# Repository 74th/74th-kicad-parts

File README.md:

# 74th の使う KiCad Parts

- symbols: KiCad のシンボル
- footprints: KiCad のフットプリント
- 3d-models: ダウンロードした 3D モデルを置くディレクトリ
- pcb-default: 基板の設定の標準データ。最初にインポートして使う

## 他によく使う KiCad Parts

- Espressif KiCad Library https://github.com/espressif/kicad-libraries

## あるもの（一例）

### シンボル

- 74th_ApplicationIC
  - CH224K: USB PD Sink Controller
  - CH334R: USB2.0 Hub Controller
  - CH340C, CH340G, CH340X: USB UART
  - CH9329: USB to USBHID Keyboard/Mouse
  - W25Q32JVSS, W25Q32JVUU: Flash
- 74th_Board
  - M5Stack Core2 M-BUS
- 74th_Display
  - OSL01561-LW: 7seg LED
  - I2C OLED Module
- 74th_Interface
  - AudioJack_4_TRRS
  - ESP-Prog_ProgramCOM_Recv
  - Grove Device-Side/Host-Side
  - I2C Breakout
  - I2C Grove Device-Side/Host-Side
  - JoyStick b10k
  - Jumper 2/3
  - Pin 1~20
  - Pin 4 PokaYoke
  - Pin 2 GND
  - ProMicro Left/Right/Left-NoGND
  - Qwiic DeviceSide/HostSide
  - RaspberryPiPico PinOut
  - SWD 3Pin
  - SWD 10Pin Debuger-Side/MCU-Side
  - SWD WCH 1Wire/With VCC/With TXD-VCC
  - SWD LinkE header
  - SW Push
  - SW Push Pin-4
  - SW Slide
  - UART Grove Device-Side/Host-Side
  - UART TX
  - USB TypeA 2.0 Plug
  - USB TypeA 2.0 Receptacle
  - USB TypeC 2.0 Plug
  - USB TypeC 2.0 Receptacle
  - USB TypeC 2.0 Receptacle Simple
  - USB TypeC 3.0 Plug
  - USB TypeC 3.0 Plug 24Pin
- 74th_MCU
  - CH32V002F4P6/F4U6/J4M6
  - CH32V003F4P6/F4U6/J4M6
  - CH32V006K8U6
  - CH32V203CxT6/F6T6
  - CH32V305FBP6
  - CH32X035G8U6
  - RP2040
  - RP2350A
  - RP2350B
  - STM32F103C8T6
  - STM32G030F6P6
- 74th_Passive
  - AMS117-3.3: Regulator
  - AP7333-LDO: Regulator
  - CH213K: USB電源保護IC
  - CH217K: USB電源保護IC
  - IRLM6402: Pch MOSFET
  - MT2492: DCDC Converter
  - SK6812MINI-E : RGB LED
  - MT2492: DCDC COnverter
- 74th_PassiceCommon
  - Crystal_GND24
  - L Directed
  - MOSFET Dural Pch

### footprint

- BatteryHolder CR2034
- Basic
  - Capacitor 0402in_1005M/0603in_1608M/0805in_2012M/1206_3216M
  - Capacitor 0603in_1608M/0805in_2012M WithSizeText
  - Register 0402in_1005M/0603in_1608M/0805in_2012M/1206_3216M
  - Register 0603in_1608M/0805in_2012M WithSizeText
  - Inductor 4.1x4.5mm
  - Inductor 0806in 2016M
- Connector
  - BoxPinHeader 2x03 P1.27 (ESP-Prog)
  - BoxPinHeader 2x05 P1.27 (SWD)
  - Grove or Qwiic Socket
  - HY-2.0 SMD 4Pin/TH-Surface 4Pin/TH Versical 4Pin
  - HalfPinHeader SWD
  - MJ-4PP-9 (TRRSジャック)
  - PH-2.0
  - SH-1.0 SMD 2Pin/4Pin(Qwiic)
  - USB-A Plug TH
  - USB-A Receptacle SMT 4-Pin
  - USB-C Plug 2.0 for 24 Pin
  - USB-C Plug 2.0 24Pin
  - USB-C Receptacle SMT 12-PIn Midmount
  - USB-C Receptacle SMT 12-PIn Midmount Simple
  - USB-C Receptacle SMT 12-PIn Simple
  - USB-Micro Plug SMD
  - USB3-A-Receptacle SMT 9-Pin
- Crystal
  - SMD 2012 2-Pin 2.0x1.2mm HandSoldering
  - SMD 2012 2-Pin 3.2x1.5mm
  - SMD 2012 4-Pin 3.2x1.5mm HandSoldering
- Display
  - OSL10561-LW
- Hole
  - M1.6
  - M2
  - M5Dial/M5Dial Stopper
  - M5StackCore2
  - OLED 0.96inch
- LED
  - 0805in_2016M
  - Reverse Mount 0805in_2016M
  - SK6812MINI-E back side light
  - SK6812MINI-E silk side light
- Mousebite
- Package
  - Fuse 1812in 4532m
  - LQFP-48 7x7mm P0.5 EP1.7x1.7mm
  - QFN-20-1EP 3x3mm P0.5 EP2.6x2.6mm Handsolder
  - QFN-24-1EP 4x4mm P0.4 EP2.8x2.8mm Handsolder
  - QFN-28-1EP 4x4mm P0.4 EP2.7x2.7mm
  - QFN-32-1EP 4x4mm P0.4 EP2.7x2.7mm
  - QFN-32-1EP 4x4mm P0.4 EP2.7x2.7mm Handsolder
  - QFN-54-1EP 7x7mm P0.4 EP3.1x3.1mm Handsolder
  - QFN-60-1EP 7x7mm P0.4 EP3.4x3.4mm Handsolder
  - QFN-80-1EP 10x10mm P0.4 EP3.4x3.4mm Handsolder
  - SOD23 Diode
  - SOD23 Diode No-Reference
  - SOD123W
  - SOIC-8 3.9x4.9mm P1.27mm
  - SOIC-8 3.25x5.23mm P1.27mm
  - SOIC-16 3.8x8.8mm P1.27mm
  - SOT-23
  - SOT-23-5
  - SOT-23-6
  - SOT-89-3
  - SOT233-3
  - TSSOP-20 4.4x6.5mm P0.65mm
  - USON-8 3.4mm P0.8mm
- Pad 1/4
- PinOut
  - Pin 1~20
  - PokeYoke
  - Raspberry Pi Pico
  - ProMicro LIKE LEFT/RIGHT
- SolderJumper-2/3
- Switch
  - MXChocSwap 1Side 1.0u
  - MXChoc 1.0u
  - MXSwapChoc 1.0u
  - MXSwap 1.0u
  - MXSwap 1.25u
  - SKRPABE010
  - SK-12D02-G020
  - TactileSwitch4Foot 6x6

## LICENSE

明記のないものは CC0 (Creative Commons Public License) とします。

いくつかのパーツは KiCad ライブラリーからコピーして使っています。それぞれのディレクトリの README を参照してください。

## Links

- 74thのOpen Source Hardwareのプロジェクト https://github.com/74th/74th-open-source-hardware-projects

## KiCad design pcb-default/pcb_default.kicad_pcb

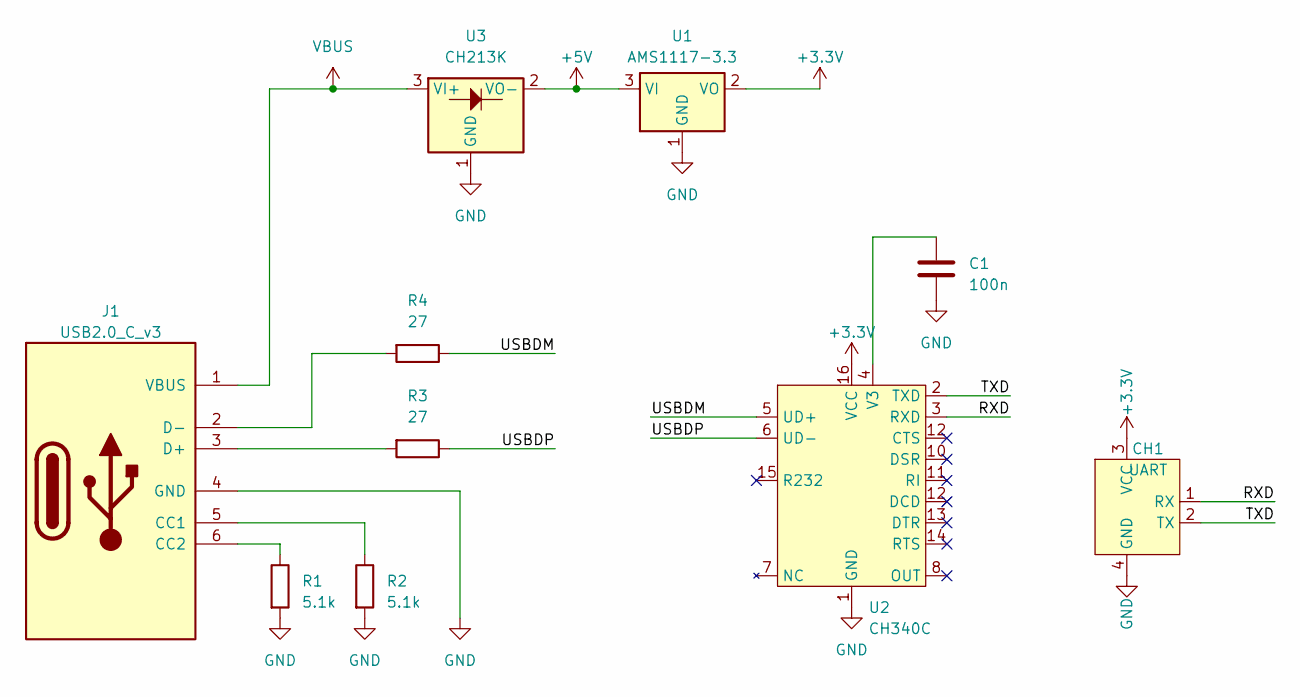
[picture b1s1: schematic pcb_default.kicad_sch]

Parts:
C1: 100n; Capacitor_0805_2012
CH1: UART; Connector_HY-2.0_SMD_4Pin
J1: USB2.0_C_v3; Connector_USB-C-Receptacle_SMT_12-Pin_Simple
R1, R2: 5.1k; Register_0805_2012
R3, R4: 27; Register_0805_2012
U1: AMS1117-3.3; Package_SOT-223-3
U2: CH340C; Package_SOIC-16_3.9x9.9mm_P1.27mm
U3: CH213K; Package_SOT-23

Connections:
+3V3: CH1.3 (VCC), U1.2 (VO), U2.16 (VCC)
+5V: U1.3 (VI), U3.2 (VO-)
/RXD: CH1.1 (RX), U2.3 (RXD)
/TXD: CH1.2 (TX), U2.2 (TXD)
/USBDM: R4.1, U2.5 (UD+)
/USBDP: R3.1, U2.6 (UD-)
GND: C1.2, CH1.4 (GND), J1.4 (GND), R1.2, R2.2, U1.1 (GND), U2.1 (GND), U3.1 (GND)
unnamed: J1.5 (CC1), R2.1
unnamed: J1.6 (CC2), R1.1
unnamed: J1.3 (D+), R3.2
unnamed: J1.2 (D-), R4.2
unnamed: C1.1, U2.4 (V3)
VBUS: J1.1 (VBUS), U3.3 (VI+)

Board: 2 copper layers, 10 parts (0 on the bottom side), 13 nets, no tracks yet.

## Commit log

2023-10-01 upload
2023-10-01 update LICENSE
2024-01-20 usb-c
2024-08-09 RP2350A, RP2350B
2026-01-24 switch
